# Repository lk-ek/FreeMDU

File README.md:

# FreeMDU

FreeMDU provides tools for Miele's optical diagnostic interface: a [protocol library](protocol/README.md), a [terminal UI](tui/README.md), and [ESP firmware](home/README.md) for a USB bridge or MQTT/Home Assistant monitoring. It is an independent alternative to the proprietary Miele Diagnostic Utility. Background on the interface is in the [original research post](https://medusalix.github.io/posts/miele-interface).

> [!CAUTION]
> Diagnostic actions can affect an appliance. This project is experimental; use write or full-access functions only when you understand the device and their effects.

## Supported devices

The appliance reports a *software ID*. FreeMDU uses that ID to select a protocol implementation; the implementation supplies its device kind, properties and actions. A software ID identifies firmware, not necessarily a unique model. Confirmed combinations:

| Software ID | Device | Board | Microcontroller | Interface | Support |
| --- | --- | --- | --- | --- | --- |
| 218 | W 985 | EDPW 213 | Mitsubishi M37451MC | Check inlet (PC) | Protocol profile |
| 324 | W 980 | EDPW 213 | Mitsubishi M37451MC | Check inlet (PC) | Protocol profile |
| 360 | Bare board | EDPW 223-A | Mitsubishi M38078MC-065FP | Check inlet (PC) | Protocol profile |
| 419 | Bare board | EDPW 206 | Mitsubishi M37451MC-804FP | Check inlet (PC) | Protocol profile |
| 469 | W 487 S | EDPW 228-A | Mitsubishi M38078MF | Check inlet (PC) | Protocol profile |
| 517 | G 7804 | EGPL 061 | Mitsubishi M38079EFFP | (PC) DOS | Protocol profile |
| 605 | G 651 I PLUS-3 | EGPL 542-C | Mitsubishi M38027M8 | Salt (PC) | Protocol profile |
| 629 | W 2446 | EDPL 126-B | Mitsubishi M38079MF-308FP | Check inlet (PC) | Protocol profile |
| 2088 | W 3241 | EDPL 162-B | Mitsubishi M38079EFFP | Check inlet (PC) | Protocol profile |
| 2895 | W 3164 | EDPL 151-B | Mitsubishi M38079MF-322FP | Check inlet (PC) | Protocol profile |
| 410 | W 307 | — | — | Optical diagnostic port | Experimental read-only monitoring |
| 498 | T 4223 C | — | — | Optical diagnostic port | Experimental read-only monitoring |

Similar models may use a compatible software ID. Query the ID before assuming compatibility.

## Choose a mode

- **Diagnostics:** flash the ESP [bridge firmware](home/README.md#firmware-modes), connect the optical adapter and run the [TUI](tui/README.md).
- **Home Assistant:** flash the [standalone firmware](home/README.md#build-and-flash). Its two IR ports poll independently and publish MQTT discovery and values.
- **Custom tools:** use the [protocol crate](protocol/README.md) with a supported transport.

The standalone firmware maps a connected protocol profile's `DeviceKind::WashingMachine` to `washer/...` and `DeviceKind::TumbleDryer` to `dryer/...`, independently of the port. The MQTT mapping currently has one channel per kind. Other device kinds are supported by the protocol/TUI but have no standalone MQTT channel. Device-specific experimental features remain limited to their respective IDs. See [Home](home/README.md#device-detection-and-mqtt) for routing, pinout, configuration and limitations.

Past receiver tests, EEPROM investigations and protocol observations are in the [historical notes](home/HISTORY.md).

## License and attribution

This project is independent of and not affiliated with Miele & Cie. KG. Product names are used only to identify compatible appliances.

Licensed under either [Apache-2.0](LICENSE-APACHE) or [MIT](LICENSE-MIT). Contributions submitted for inclusion are dual licensed under the same terms unless explicitly stated otherwise.

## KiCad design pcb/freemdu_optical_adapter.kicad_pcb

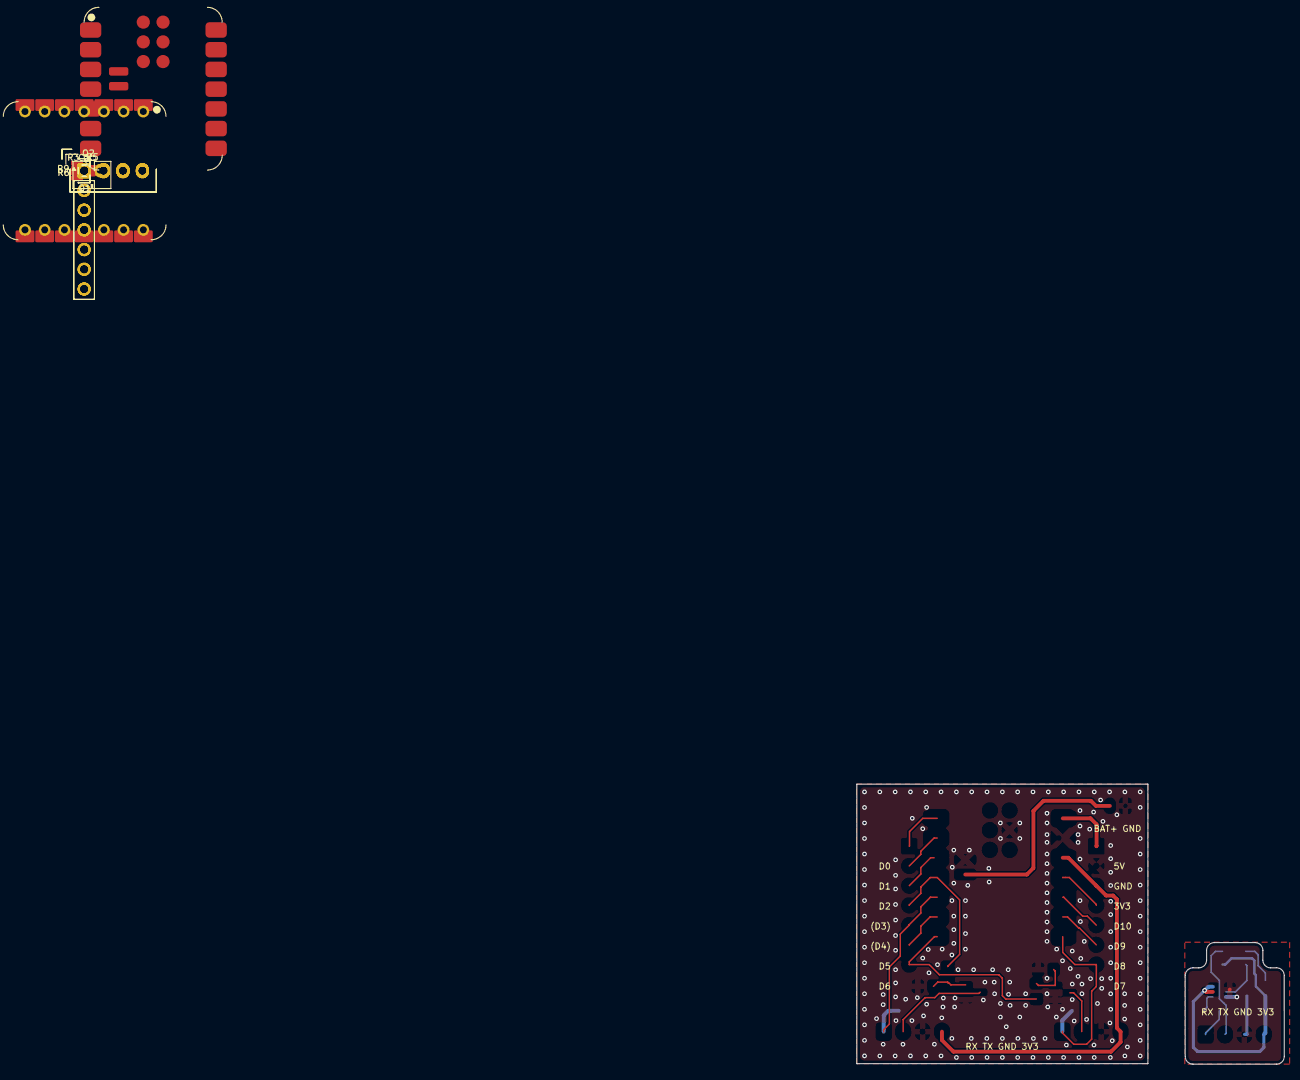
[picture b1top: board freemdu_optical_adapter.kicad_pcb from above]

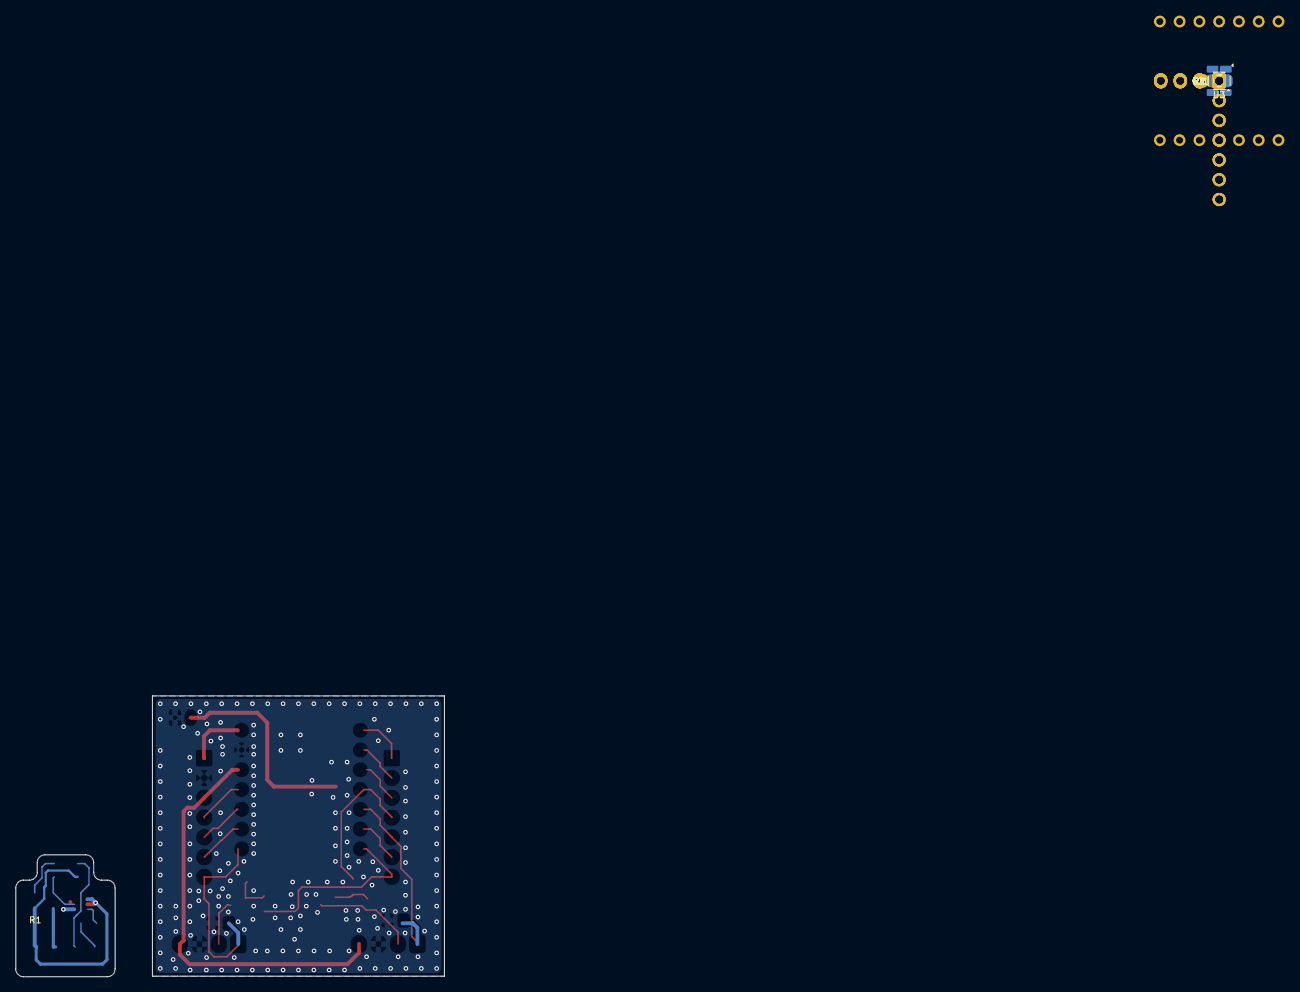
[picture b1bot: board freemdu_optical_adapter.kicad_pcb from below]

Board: 2 copper layers, 55.1 x 36.1 mm, 22 parts (7 on the bottom side), 22 nets.

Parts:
A1: XIAO_ESP32C3; XIAO-ESP32-C3-DIP
A1#2: XIAO_ESP32C3; XIAO-ESP32-C3-SMD
C1: 100n; C_0805_2012Metric_Pad1.18x1.45mm_HandSolder
C2, C3: 330p; C_0805_2012Metric_Pad1.18x1.45mm_HandSolder
J1, J2, J6: Conn_01x04; JST_XH_B4B-XH-A_1x04_P2.50mm_Vertical
J3, J4: Conn_01x07; PinSocket_1x07_P2.54mm_Vertical
J5: Conn_01x02; JST_PH_B2B-PH-K_1x02_P2.00mm_Vertical
Q1, Q2: BSS138; SOT-23
R1, R3, R5: 100R; R_0805_2012Metric_Pad1.20x1.40mm_HandSolder
R2: 15k; R_0805_2012Metric_Pad1.20x1.40mm_HandSolder
R4: 68; R_0805_2012Metric_Pad1.20x1.40mm_HandSolder
R6, R9: 47k; R_0805_2012Metric_Pad1.20x1.40mm_HandSolder
U1: SFH7250; SFH7250_Multi_TOPLED
U3: 74LVC1G17GW,125; SOT-353_SC-70-5

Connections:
+3V3: A1.12 (3V3_OUT), A1#2.12 (3V3_OUT), C1.1, J1.4, J2.4, J4.3, J6.4, R1.1, U1.3 (C_PT), U3.5 (VCC)
+5V: A1.14 (VBUS), A1#2.14 (VBUS), J4.1
/IR2_RX_D7: A1.8 (D7), A1#2.8 (D7), C3.1, J1.1, J4.7
/IR2_TX: J1.2, Q2.3 (D)
/IR2_TX_D6: A1.7 (D6), A1#2.7 (D6), J3.7, R5.1
/IR_RX_D4: A1.5 (D4), A1#2.5 (D4), C2.1, J2.1, J3.5, J6.1, R4.2
/IR_RX_RAW: R2.1, U1.4 (E_PT), U3.2
/IR_TX: J2.2, J6.2, Q1.3 (D), U1.2 (K_LED)
/IR_TX_D3: A1.4 (D3), A1#2.4 (D3), J3.4, R3.1
GND: A1.13 (GND), A1#2.13 (GND), A1#2.18 (GND), A1#2.22 (GND), C1.2, C2.2, C3.2, J1.3, J2.3, J4.2, J5.1, J6.3, Q1.2 (S), Q2.2 (S), R2.2, R6.1, R9.1, U3.3 (GND)
unnamed: A1.1 (D0), A1#2.1 (D0), J3.1
unnamed: A1.2 (D1), A1#2.2 (D1), J3.2
unnamed: A1.3 (D2), A1#2.3 (D2), J3.3
unnamed: A1.6 (D5), A1#2.6 (D5), J3.6
unnamed: A1.9 (D8), A1#2.9 (D8), J4.6
unnamed: A1.10 (D9/BOOT), A1#2.10 (D9/BOOT), J4.5
unnamed: A1.11 (D10), A1#2.11 (D10), J4.4
unnamed: A1#2.21 (VBAT), J5.2
unnamed: Q1.1 (G), R3.2, R6.2
unnamed: Q2.1 (G), R5.2, R9.2
unnamed: R4.1, U3.4
unnamed: R1.2, U1.1 (A_LED)
